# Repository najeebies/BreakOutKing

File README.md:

This repo contains the hardware, testing firmware, and plans for all the connector breakouts

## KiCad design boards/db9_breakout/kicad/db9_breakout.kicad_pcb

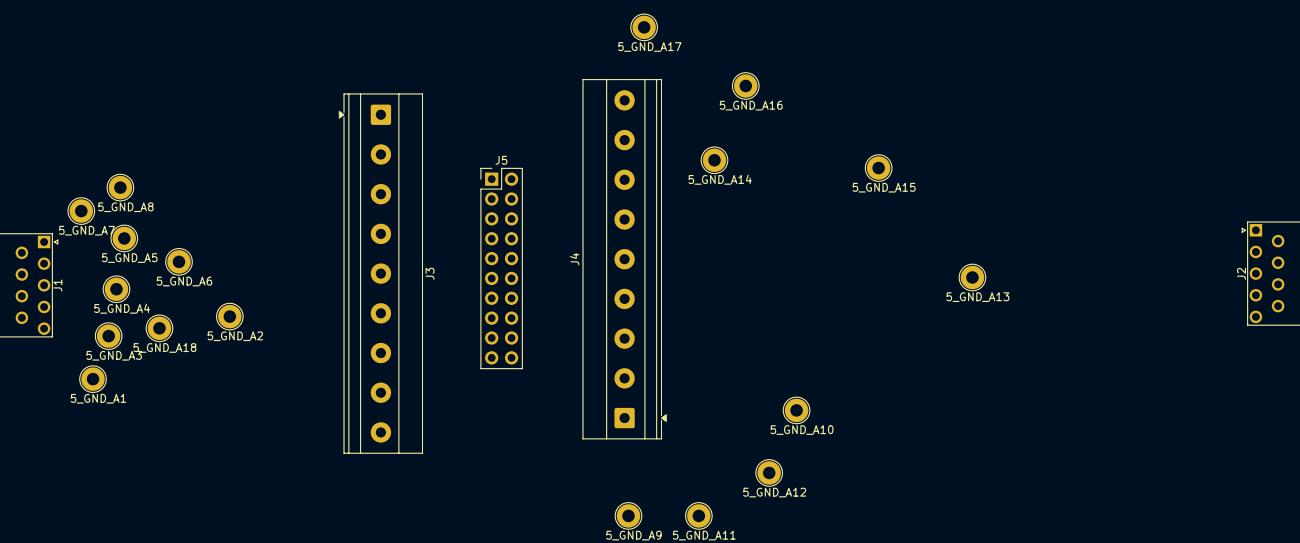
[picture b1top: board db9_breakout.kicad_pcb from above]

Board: 2 copper layers, 23 parts (0 on the bottom side), 18 nets, no tracks yet.

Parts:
5_GND_A1, 5_GND_A2, 5_GND_A3, 5_GND_A4, 5_GND_A5, 5_GND_A6, 5_GND_A7, 5_GND_A8, 5_GND_A9, 5_GND_A10, 5_GND_A11, 5_GND_A12, 5_GND_A13, 5_GND_A14, 5_GND_A15, 5_GND_A16, 5_GND_A17, 5_GND_A18: TestPoint; TestPoint_Loop_D2.60mm_Drill1.6mm_Beaded
J1: DE9_Pins; DSUB-9_Pins_Horizontal_P2.77x2.84mm_EdgePinOffset9.40mm
J2: DE9_Socket; DSUB-9_Socket_Horizontal_P2.77x2.84mm_EdgePinOffset9.40mm
J3, J4: Screw_Terminal_01x09; TerminalBlock_Phoenix_MKDS-1,5-9-5.08_1x09_P5.08mm_Horizont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
J5: Conn_02x10_Row_Letter_First; PinHeader_2x10_P2.54mm_Vertical

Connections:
/1_DCD_A: 5_GND_A8.1 (1_1), J1.1, J3.9
/1_DCD_B: 5_GND_A17.1 (1_1), J2.1, J4.9
/2_RX_A: 5_GND_A6.1 (1_1), J1.2, J3.7
/2_RX_B: 5_GND_A15.1 (1_1), J2.2, J4.7
/3_TX_A: 5_GND_A4.1 (1_1), J1.3, J3.5
/3_TX_B: 5_GND_A13.1 (1_1), J2.3, J4.5
/4_DTR_A: 5_GND_A2.1 (1_1), J1.4, J3.3
/4_DTR_B: 5_GND_A11.1 (1_1), J2.4, J4.3
/5_GND_A: 5_GND_A18.1 (1_1), J1.5, J3.1
/5_GND_B: 5_GND_A9.1 (1_1), J2.5, J4.1
/6_DSR_A: 5_GND_A7.1 (1_1), J1.6, J3.8
/6_DSR_B: 5_GND_A16.1 (1_1), J2.6, J4.8
/7_RTS_A: 5_GND_A5.1 (1_1), J1.7, J3.6
/7_RTS_B: 5_GND_A14.1 (1_1), J2.7, J4.6
/8_CTS_A: 5_GND_A3.1 (1_1), J1.8, J3.4
/8_CTS_B: 5_GND_A12.1 (1_1), J2.8, J4.4
/9_RI_A: 5_GND_A1.1 (1_1), J1.9, J3.2
/9_RI_B: 5_GND_A10.1 (1_1), J2.9, J4.2

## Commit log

2026-05-22 Add project description to README
2026-06-21 file structure created for breakout repo
2026-06-21 component schematic done, need nets
2026-06-22 schematic finished, need footprint assignment
2026-06-22 footprint assigned, board started
